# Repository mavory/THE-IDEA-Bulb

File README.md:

# "THE IDEA." Bulb
My project in the shape of a bulb with 10 LEDs that are placed around it!

### Why did I do this?

I wanted to take a break and create a project that wouldn't take so long... So I created this project!

## KiCad things:
Here are pictures of the schematic and PCB I created in KiCad!
### PCB:

### Schematic:

## BOM

| Reference | Value / Type | Qty | Description |
| :--- | :--- | :---: | :--- |
| **U1** | NE555P | 1 | Timer |
| **U2** | 4017 | 1 | Coun
| **D1 - D10** | LEDs | 10 | Standard LED |
| **C1** | 1 µF | 1 | Electrolytic Capacitor |
| **C2** | 0.01 µF | 1 | Ceramic Capacitor |
| **R1** | 470 Ω | 1 | Resistor |
| **R2** | 1 kΩ | 1 | Resistor |
| **RV1** | 50 kΩ | 1 | Potentiometer (Speed ​​​​control) |
| **J1** | Power| 1 | Power Header (2-pin) |
| **J2** | Debug / Signal | 1 | Signal Output Pin |
|        |                |   |                    |
| **PCB** | Black | With shipping | 3.50 USD |

## Project

Here is a video, it works: https://youtube.com/shorts/iOuM33JNCGg?is=_r2Ftzi8CJoQdTDR

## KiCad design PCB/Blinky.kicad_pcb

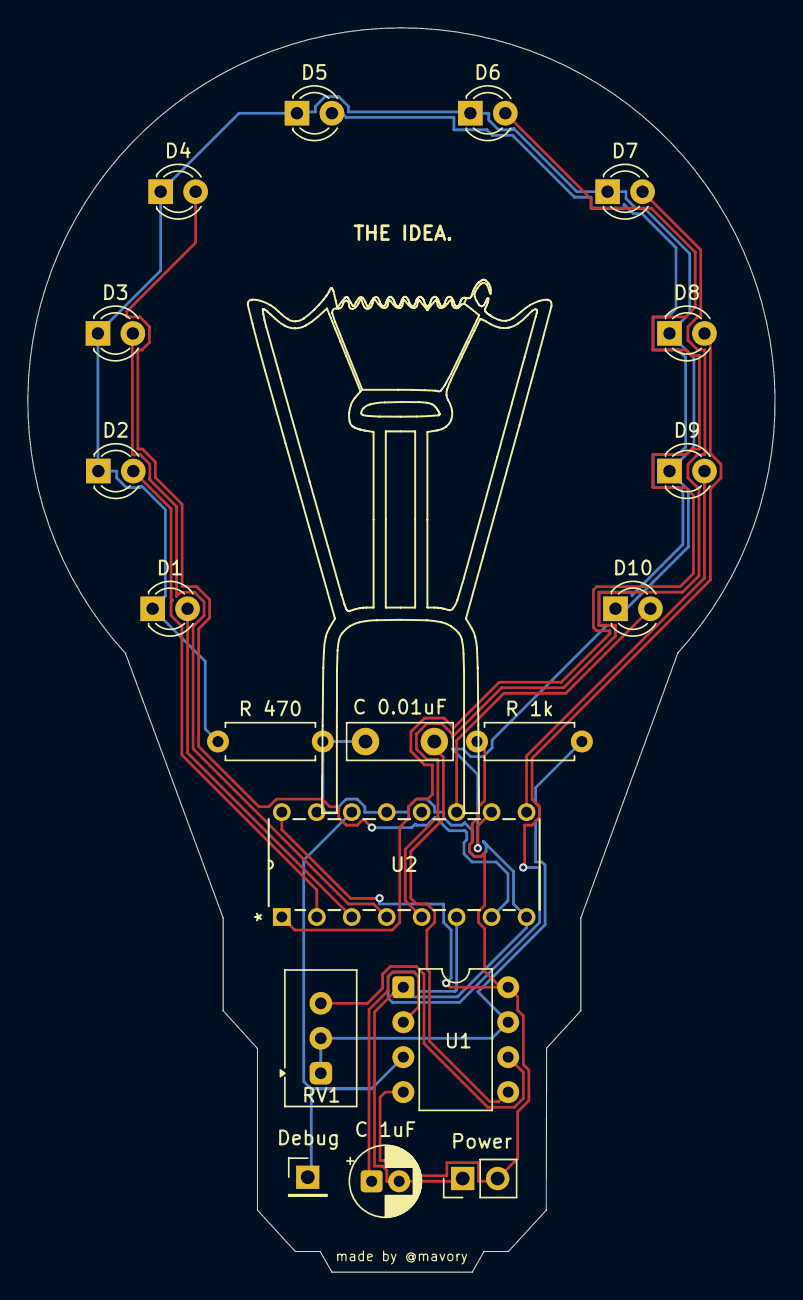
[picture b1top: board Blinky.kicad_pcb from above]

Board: 2 copper layers, 54.3 x 90.4 mm, 19 parts (0 on the bottom side), 18 nets.

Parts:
C 0.01uF: 0.01 uF; C_Disc_D7.5mm_W2.5mm_P5.00mm
C 1uF: 1 uF; CP_Radial_D5.0mm_P2.00mm
D1, D2, D3, D4, D5, D6, D7, D8, D9, D10: LED; LED_D3.0mm
Debug: Debug; PinHeader_1x01_P2.54mm_Vertical
Power: Power; PinHeader_1x02_P2.54mm_Vertical
R 1k: 1k; R_Axial_DIN0207_L6.3mm_D2.5mm_P7.62mm_Horizontal
R 470: 470; R_Axial_DIN0207_L6.3mm_D2.5mm_P7.62mm_Horizontal
RV1: 50k; Potentiometer_Vishay_T93YA_Vertical
U1: NE555P; DIP-8_W7.62mm
U2: 4017; N16

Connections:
+5V: Power.2, R 1k.1, U1.4 (R), U1.8 (VCC), U2.16 (VDD)
GND: C 0.01uF.1, C 1uF.2, Power.1, R 470.2, U1.1 (GND), U2.8 (VSS), U2.13 (CKEN), U2.15 (Reset)
unnamed: D1.2 (A), U2.3 (Q0)
unnamed: D1.1 (K), D2.1 (K), D3.1 (K), D4.1 (K), D5.1 (K), D6.1 (K), D7.1 (K), D8.1 (K), D9.1 (K), D10.1 (K), R 470.1
unnamed: D2.2 (A), U2.2 (Q1)
unnamed: D3.2 (A), U2.4 (Q2)
unnamed: D4.2 (A), U2.7 (Q3)
unnamed: D5.2 (A), U2.10 (Q4)
unnamed: D6.2 (A), U2.1 (Q5)
unnamed: D7.2 (A), U2.5 (Q6)
unnamed: D8.2 (A), U2.6 (Q7)
unnamed: D9.2 (A), U2.9 (Q8)
unnamed: D10.2 (A), U2.11 (Q9)
unnamed: C 0.01uF.2, U1.5 (CV)
unnamed: R 1k.2, RV1.1, RV1.2, U1.7 (DIS)
unnamed: RV1.3, U1.6 (THR)
unnamed: C 1uF.1, U1.2 (TR)
Signal: Debug.1, U1.3 (Q), U2.14 (CLK)

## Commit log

2026-02-08 Create h
2026-02-08 Circuit diagram
2026-02-08 README.md
    Updated project description and added images for PCB and schematic.
2026-02-08 README.md
    Added a section about KiCad with images of the schematic and PCB.
2026-02-08 README.md
2026-02-08 BOM.csv
2026-02-08 Photos
2026-02-08 README.md
    Added PCB information to the components list.
2026-02-08 Booooooommmmmmm
2026-03-14 Add project section with image
    Added project section with image to README.
2026-03-14 Document progress on Blinky board project
    Updated the journal with detailed progress on the Blinky board project, including sketches, PCB design, and assembly challenges.
